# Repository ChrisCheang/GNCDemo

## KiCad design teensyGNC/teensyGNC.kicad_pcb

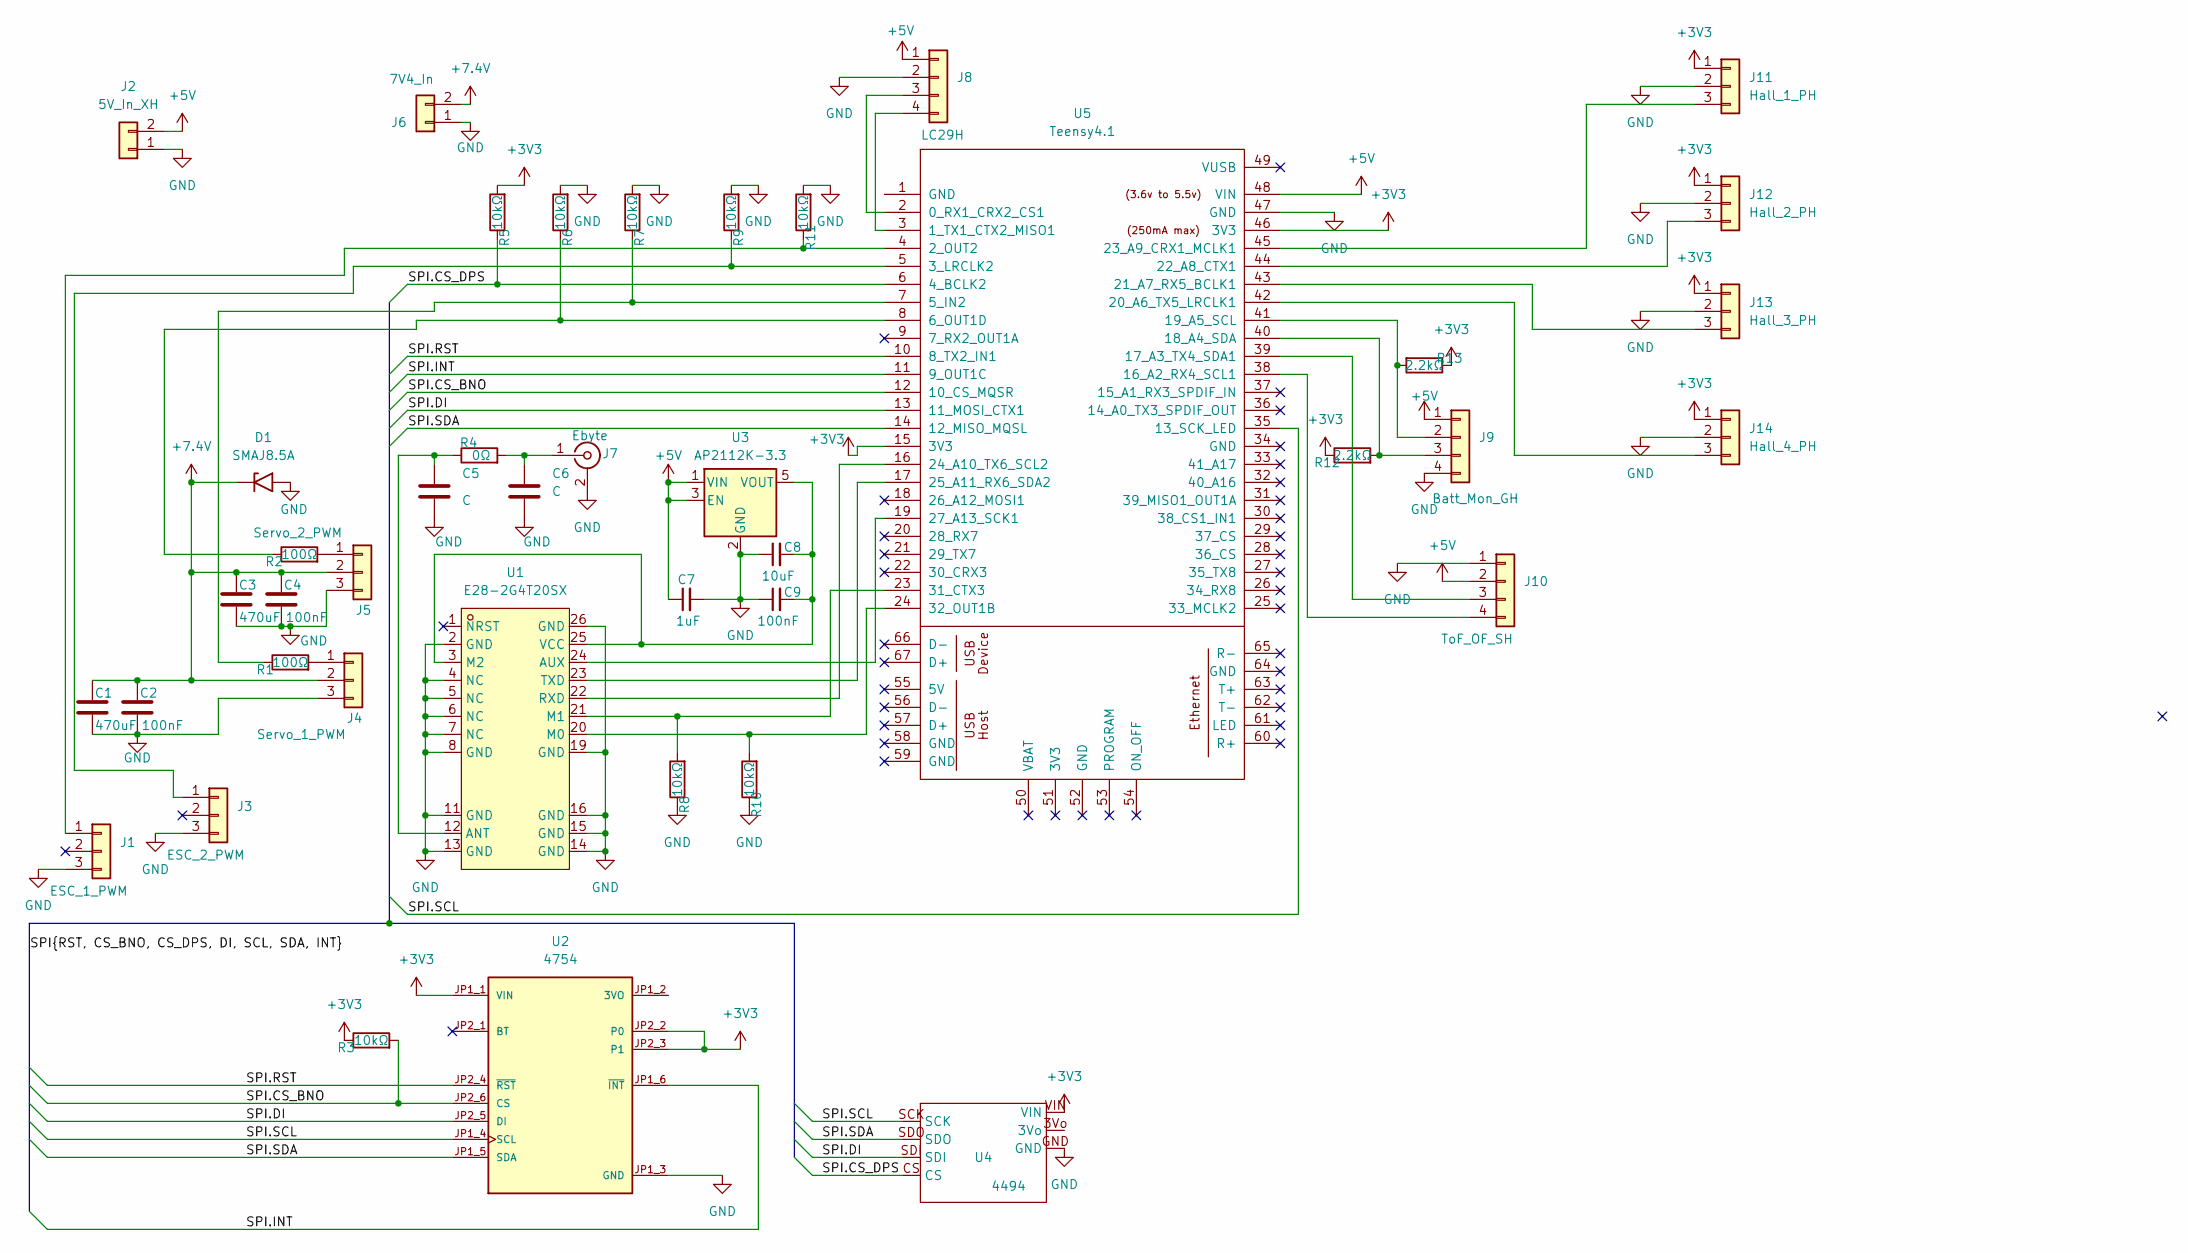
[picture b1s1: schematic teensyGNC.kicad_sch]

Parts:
C1, C3: 470uF; CP_EIA-7343-43_Kemet-X; LCSC Part # C7234
C2, C4, C9: 100nF; C_0603_1608Metric; LCSC Part # C14663
C5, C6: C; C_0603_1608Metric
C7: 1uF; C_0603_1608Metric; LCSC Part # C29936
C8: 10uF; C_0603_1608Metric; LCSC Part # C109457
D1: SMAJ8.5A; D_SMA; LCSC Part # C135018
J1: ESC_1_PWM; PinHeader_1x03_P2.54mm_Vertical
J2: 5V_In_XH; JST_XH_B2B-XH-AM_1x02_P2.50mm_Vertical; LCSC Part # C158012
J3: ESC_2_PWM; PinHeader_1x03_P2.54mm_Vertical
J4: Servo_1_PWM; PinHeader_1x03_P2.54mm_Vertical
J5: Servo_2_PWM; PinHeader_1x03_P2.54mm_Vertical
J6: 7V4_In; AMASS_XT30UPB-M_1x02_P5.0mm_Vertical; LCSC Part # C428721
J7: Ebyte; SMA_BAT_Wireless_BWSMA-KWE-Z001; LCSC Part # C496551
J8: LC29H; PinHeader_1x04_P2.54mm_Vertical
J9: Batt_Mon_GH; JST_GH_BM04B-GHS-TBT_1x04-1MP_P1.25mm_Vertical; LCSC Part # C161692
J10: ToF_OF_SH; JST_SH_BM04B-SRSS-TB_1x04-1MP_P1.00mm_Vertical; LCSC Part # C160390
J11: Hall_1_PH; JST_PH_B3B-PH-K_1x03_P2.00mm_Vertical; LCSC Part # C131339
J12: Hall_2_PH; JST_PH_B3B-PH-K_1x03_P2.00mm_Vertical; LCSC Part # C131339
J13: Hall_3_PH; JST_PH_B3B-PH-K_1x03_P2.00mm_Vertical; LCSC Part # C131339
J14: Hall_4_PH; JST_PH_B3B-PH-K_1x03_P2.00mm_Vertical; LCSC Part # C131339
R1, R2: 100Ω; R_0603_1608Metric; LCSC Part # C122970
R3, R5, R6, R7, R8, R9, R10, R11: 10kΩ; R_0603_1608Metric; LCSC Part # C25804
R4: 0Ω; R_0603_1608Metric; LCSC Part # C95177
R12, R13: 2.2kΩ; R_0603_1608Metric; LCSC Part # C4190
U1: E28-2G4T20SX; COMM-SMD_E28-2G4T20SX; MPN E28-2G4T20SX; LCSC Part # C42464206
U2: 4754; MODULE_4754; PARTREV 2021-03-16
U3: AP2112K-3.3; SOT-23-5; LCSC Part # C51118
U4: 4494; MODULE_4494
U5: Teensy4.1; Teensy41

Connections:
+3V3: J11.1, J12.1, J13.1, J14.1, R3.1, R5.2, R12.1, R13.1, U2.JP1_1 (VIN), U2.JP2_2 (P0), U2.JP2_3 (P1), U4.VIN, U5.15 (3V3), U5.46 (3V3)
+5V: C7.1, J2.2, J8.1, J9.1, J10.2, U3.1 (VIN), U3.3 (EN), U5.48 (VIN)
+7.4V: C1.1, C2.1, C3.1, C4.1, D1.1 (A1), J4.2, J5.2, J6.2
/SPI.CS_BNO: R3.2, U2.JP2_6 (CS), U5.12 (10_CS_MQSR)
/SPI.CS_DPS: R5.1, U4.CS, U5.6 (4_BCLK2)
/SPI.DI: U2.JP2_5 (DI), U4.SDI, U5.13 (11_MOSI_CTX1)
/SPI.INT: U2.JP1_6 (~INT), U5.11 (9_OUT1C)
/SPI.RST: U2.JP2_4 (~RST), U5.10 (8_TX2_IN1)
/SPI.SCL: U2.JP1_4 (SCL), U4.SCK, U5.35 (13_SCK_LED)
/SPI.SDA: U2.JP1_5 (SDA), U4.SDO, U5.14 (12_MISO_MQSL)
GND: C1.2, C2.2, C3.2, C4.2, C5.2, C6.2, C7.2, C8.1, C9.1, D1.2 (A2), J1.3, J2.1, J3.3, J4.3, J5.3, J6.1, J7.2 (Ext), J8.2, J9.4, J10.1, J11.2, J12.2, J13.2, J14.2, R6.2, R7.2, R8.1, R9.2, R10.1, R11.2, U1.2 (GND), U1.4 (NC), U1.5 (NC), U1.6 (NC), U1.7 (NC), U1.8 (GND), U1.11 (GND), U1.13 (GND), U1.14 (GND), U1.15 (GND), U1.16 (GND), U1.19 (GND), U1.26 (GND), U2.JP1_3 (GND), U3.2 (GND), U4.GND, U5.47 (GND)
unnamed: J1.1, R11.1, U5.4 (2_OUT2)
unnamed: J3.1, R9.1, U5.5 (3_LRCLK2)
unnamed: J4.1, R1.2
unnamed: J5.1, R2.2
unnamed: C6.1, J7.1 (In), R4.2
unnamed: J8.3, U5.2 (0_RX1_CRX2_CS1)
unnamed: J8.4, U5.3 (1_TX1_CTX2_MISO1)
unnamed: J9.2, R13.2, U5.41 (19_A5_SCL)
unnamed: J9.3, R12.2, U5.40 (18_A4_SDA)
unnamed: J10.3, U5.39 (17_A3_TX4_SDA1)
unnamed: J10.4, U5.38 (16_A2_RX4_SCL1)
unnamed: J11.3, U5.45 (23_A9_CRX1_MCLK1)
unnamed: J12.3, U5.44 (22_A8_CTX1)
unnamed: J13.3, U5.43 (21_A7_RX5_BCLK1)
unnamed: J14.3, U5.42 (20_A6_TX5_LRCLK1)
unnamed: C5.1, R4.1, U1.12 (ANT)
unnamed: U1.24 (AUX), U5.19 (27_A13_SCK1)
unnamed: R10.2, U1.20 (M0), U5.24 (32_OUT1B)
unnamed: R8.2, U1.21 (M1), U5.23 (31_CTX3)
unnamed: C8.2, C9.2, U1.3 (M2), U1.25 (VCC), U3.5 (VOUT)
unnamed: U1.22 (RXD), U5.16 (24_A10_TX6_SCL2)
unnamed: U1.23 (TXD), U5.17 (25_A11_RX6_SDA2)
unnamed: R1.1, R7.1, U5.7 (5_IN2)
unnamed: R2.1, R6.1, U5.8 (6_OUT1D)

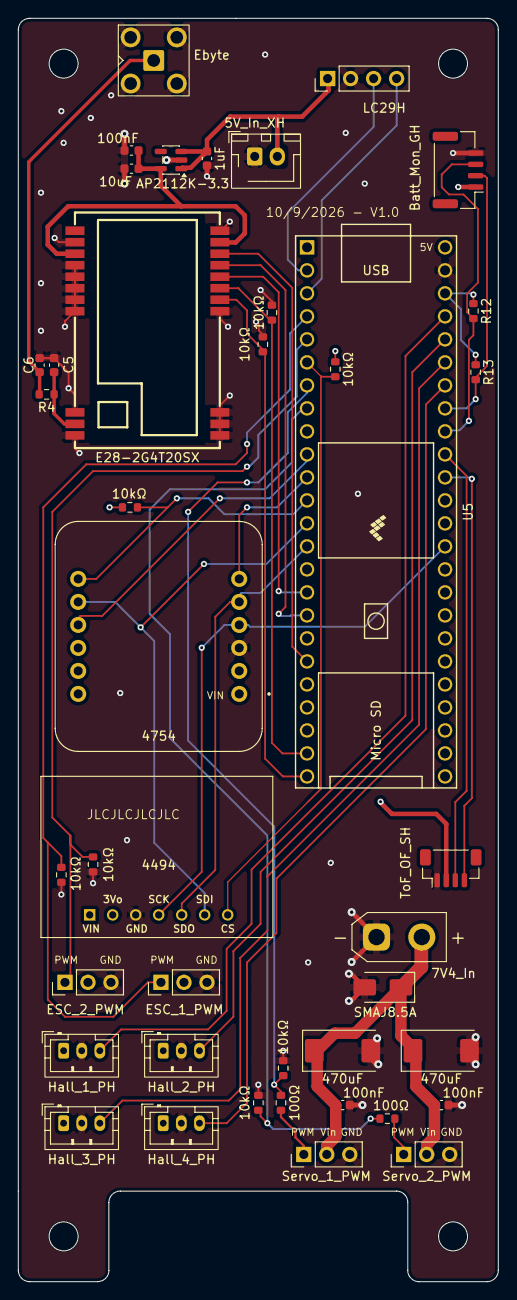
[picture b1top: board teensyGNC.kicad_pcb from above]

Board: 4 copper layers, 53.0 x 139.5 mm, 42 parts (0 on the bottom side), 35 nets.

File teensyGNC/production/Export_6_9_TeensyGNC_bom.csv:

Designator,Footprint,Quantity,Value,LCSC Part #
"C1, C3",CP_EIA-7343-43_Kemet-X,2,470uF,C7234
"C2, C4, C9",0603,3,100nF,C14663
"C5, C6",0603,2,C,
C7,0603,1,1uF,C559769
C8,0603,1,10uF,C109457
D1,D_SMA,1,SMAJ8.5A,C135018
J1,PinHeader_1x03_P2.54mm_Vertical,1,ESC_1_PWM,
J10,JST_SH_BM04B-SRSS-TB_1x04-1MP_P1.00mm_Vertical,1,ToF_OF_SH,C160390
J11,JST_PH_B3B-PH-K_1x03_P2.00mm_Vertical,1,Hall_1_PH,C131339
J12,JST_PH_B3B-PH-K_1x03_P2.00mm_Vertical,1,Hall_2_PH,C131339
J13,JST_PH_B3B-PH-K_1x03_P2.00mm_Vertical,1,Hall_3_PH,C131339
J14,JST_PH_B3B-PH-K_1x03_P2.00mm_Vertical,1,Hall_4_PH,C131339
J2,JST_XH_B2B-XH-AM_1x02_P2.50mm_Vertical,1,5V_In_XH,C158012
J3,PinHeader_1x03_P2.54mm_Vertical,1,ESC_2_PWM,
J4,PinHeader_1x03_P2.54mm_Vertical,1,Servo_1_PWM,
J5,PinHeader_1x03_P2.54mm_Vertical,1,Servo_2_PWM,
J6,AMASS_XT30UPB-M_1x02_P5.0mm_Vertical,1,7V4_In,C428721
J7,SMA_Amphenol_132203-12_Horizontal,1,Ebyte,C6962402
J8,PinHeader_1x04_P2.54mm_Vertical,1,LC29H,
J9,JST_GH_BM04B-GHS-TBT_1x04-1MP_P1.25mm_Vertical,1,Batt_Mon_GH,C161692
"R1, R2",0603,2,100Ω,C122970
"R10, R11, R3, R5, R6, R7, R8, R9",0603,8,10kΩ,C5362358
"R12, R13",0603,2,2.2kΩ,C4190
R4,0603,1,0Ω,C17168
U1,COMM-SMD_E28-2G4T20SX,1,E28-2G4T20SX,C42464206
U2,MODULE_4754,1,4754,
U3,SOT-23-5,1,AP2112K-3.3,C51118
U4,MODULE_4494,1,4494,
U5,Teensy41,1,Teensy4.1,
